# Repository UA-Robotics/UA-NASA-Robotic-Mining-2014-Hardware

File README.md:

# UA-NASA-Robotic-Mining-2014-Hardware

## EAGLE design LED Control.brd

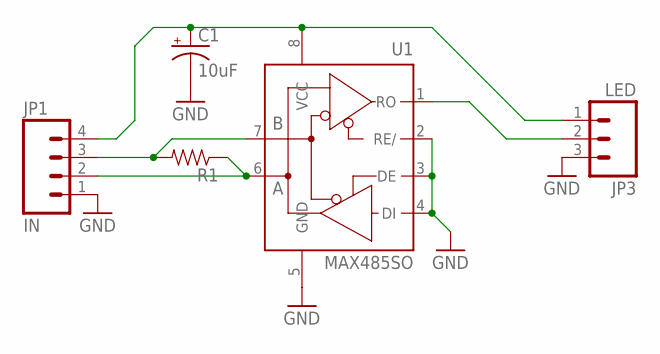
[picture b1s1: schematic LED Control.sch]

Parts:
C1: 10uF; EIA3216
JP1: IN; MOLEX-1X4_LOCK
JP3: LED; 1X03_LOCK
R1: RESISTOR0805-RES; 0805
U1: MAX485SO; SO08

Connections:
GND: C1.C (-), JP1.1, JP3.3, U1.2 (RE/), U1.3 (DE), U1.4 (DI), U1.5 (GND)
unnamed: JP1.3, R1.2, U1.7 (B)
unnamed: JP1.2, R1.1, U1.6 (A)
unnamed: C1.A (+), JP1.4, JP3.1, U1.8 (VCC)
unnamed: JP3.2, U1.1 (RO)

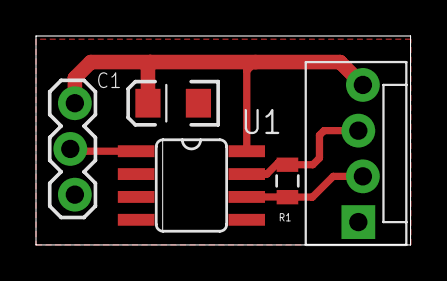
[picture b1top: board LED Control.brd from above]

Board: 2 copper layers, 20.8 x 11.6 mm, 5 parts (0 on the bottom side), 5 nets.

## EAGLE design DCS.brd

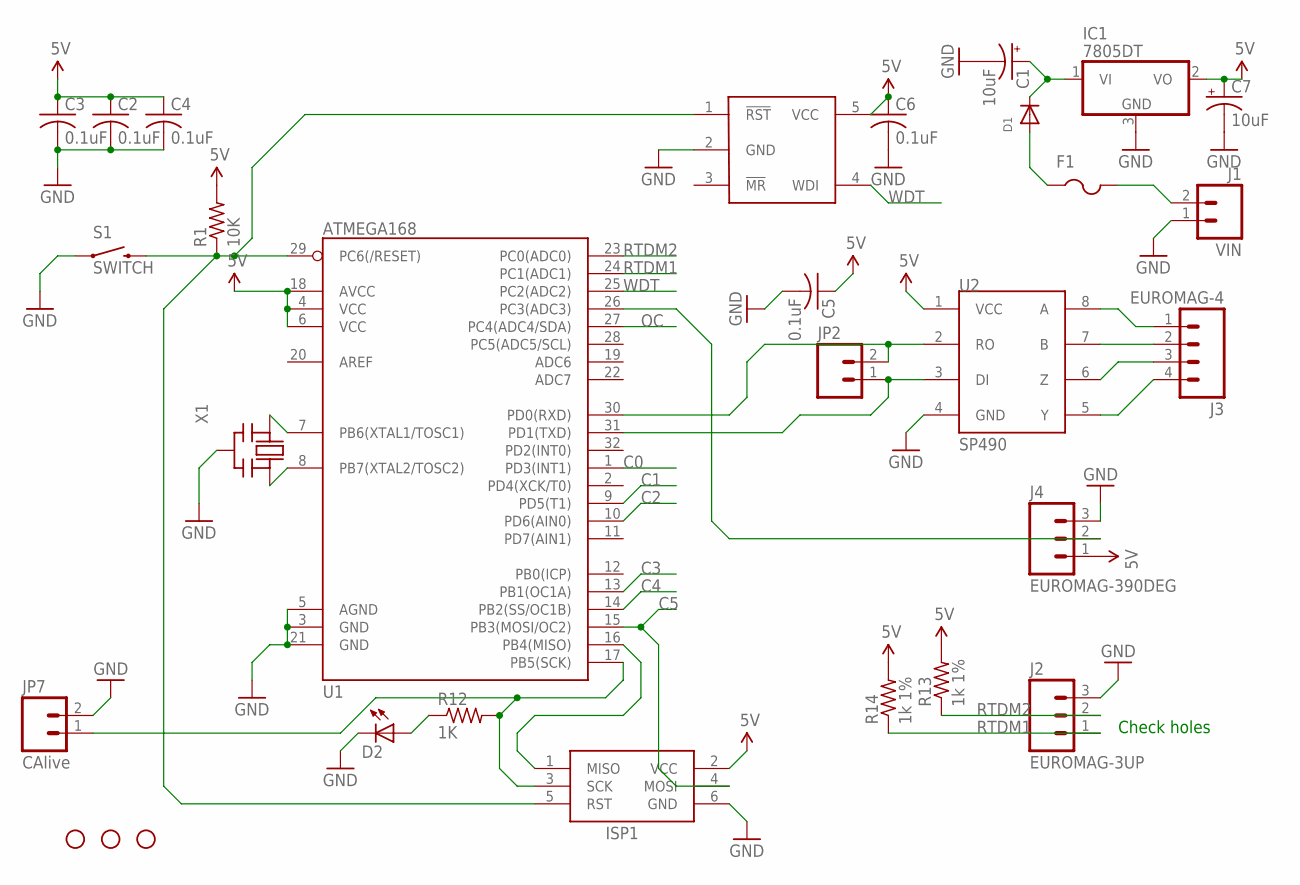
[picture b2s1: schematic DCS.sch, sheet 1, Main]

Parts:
C1: 10uF; CT6032
C2, C3, C4, C5, C6: 0.1uF; C0805
C7: 10uF; CT3216
D1: DIODESMA; SMADIODE
D2: LEDCHIPLED_0805; CHIPLED_0805
F1: PTCFUSE-1206; R1206
IC1: 7805DT; TO252
ISP1: AVRISP-6; AVRISP
J1: VIN; M2
J2: EUROMAG-3UP; M3-UP
J3: EUROMAG-4; M4
J4: EUROMAG-390DEG; M3
JP1, JP3, JP5: STAND-OFF
JP2: M02LOCK; 1X02_LOCK
JP7: CAlive; MOLEX-1X2_LOCK
R1: 10K; M0805
R12: 1K; M0805
R13, R14: 1k 1%; M0805
S1: SWITCH; TACTILE-PTH
U1: ATMEGA168; TQFP32-08
U2: SP490; SO08
U3: MAX823; SOT23-5L
X1: CERMOSCILL-AWCSR; AWCSR

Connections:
5V: C2.1, C3.1, C4.1, C5.1, C6.1, C7.+, IC1.2 (VO), ISP1.2 (VCC), J4.1, R1.2, R13.2, R14.2, U1.4 (VCC), U1.6 (VCC), U1.18 (AVCC), U2.1 (VCC), U3.5 (VCC); also elsewhere on the board
C0: U1.1 (PD3(INT1)); also elsewhere on the board
C1: U1.9 (PD5(T1)); also elsewhere on the board
C2: U1.10 (PD6(AIN0)); also elsewhere on the board
C3: U1.13 (PB1(OC1A)); also elsewhere on the board
C4: U1.14 (PB2(SS/OC1B)); also elsewhere on the board
C5: ISP1.4 (MOSI), U1.15 (PB3(MOSI/OC2)); also elsewhere on the board
GND: C1.-, C2.2, C3.2, C4.2, C5.2, C6.2, C7.-, D2.C, IC1.3 (GND), ISP1.6 (GND), J1.1, J2.3, J4.3, JP7.2, S1.1, U1.3 (GND), U1.5 (AGND), U1.21 (GND), U2.4 (GND), U3.2 (GND), X1.2 (GND); also elsewhere on the board
unnamed: JP2.2, U1.30 (PD0(RXD)), U2.2 (RO)
unnamed: F1.2, J1.2
unnamed: JP2.1, U1.31 (PD1(TXD)), U2.3 (DI)
unnamed: ISP1.5 (RST), R1.1, S1.3 (2), U1.29 (PC6(/RESET)), U3.1 (!RST)
unnamed: U1.8 (PB7(XTAL2/TOSC2)), X1.3 (OUT)
unnamed: J3.1, U2.8 (A)
unnamed: ISP1.1 (MISO), U1.16 (PB4(MISO))
unnamed: D1.A, F1.1
unnamed: U1.7 (PB6(XTAL1/TOSC1)), X1.1 (IN)
unnamed: D2.A, R12.1
unnamed: J3.2, U2.7 (B)
unnamed: J3.3, U2.6 (Z)
unnamed: C1.+, D1.C, IC1.1 (VI)
unnamed: J3.4, U2.5 (Y)
unnamed: J4.2, U1.26 (PC3(ADC3))
OC: U1.27 (PC4(ADC4/SDA)); also elsewhere on the board
RTDM1: J2.1, R14.1, U1.24 (PC1(ADC1))
RTDM2: J2.2, R13.1, U1.23 (PC0(ADC0))
SCLK: ISP1.3 (SCK), JP7.1, R12.2, U1.17 (PB5(SCK))
WDT: U1.25 (PC2(ADC2)), U3.4 (WDI)

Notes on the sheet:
Check holes

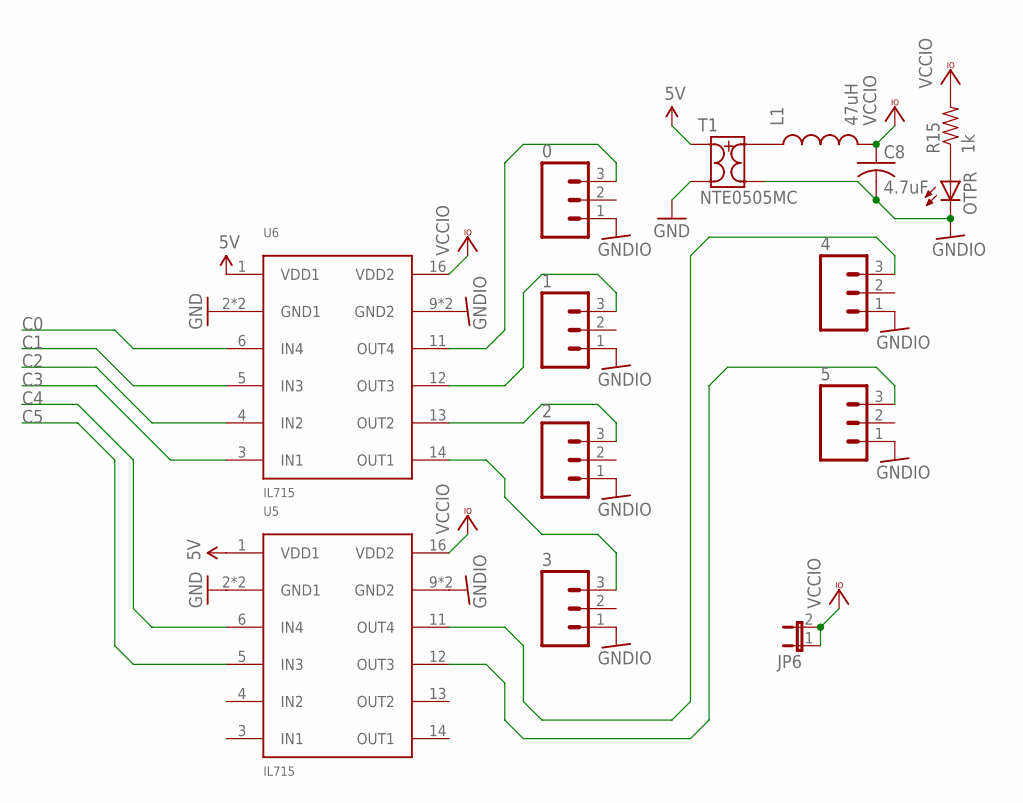
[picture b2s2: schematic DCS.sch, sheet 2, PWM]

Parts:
0, 1, 2, 3, 4, 5: M03PTH; 1X03
C8: 4.7uF; C0805
JP6: JUMPER-2SMD-NO; SJ_2S-NO
L1: 47uH; 0805
OTPR: LEDCHIP-LED0805; CHIP-LED0805
R15: 1k; 0805
T1: NTE0505MC; SO-8FT
U5, U6: IL715; S016

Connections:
5V: T1.3 (1), U5.1 (VDD1), U6.1 (VDD1); also elsewhere on the board
C0: U6.6 (IN4); also elsewhere on the board
C1: U6.5 (IN3); also elsewhere on the board
C2: U6.4 (IN2); also elsewhere on the board
C3: U6.3 (IN1); also elsewhere on the board
C4: U5.6 (IN4); also elsewhere on the board
C5: U5.5 (IN3); also elsewhere on the board
GND: T1.1 (2), U5.2 (GND1), U5.8 (GND1), U6.2 (GND1), U6.8 (GND1); also elsewhere on the board
GNDIO: 0.1, 1.1, 2.1, 3.1, 4.1, 5.1, C8.2, OTPR.C, T1.7 (3), U5.9 (GND2), U5.15 (GND2), U6.9 (GND2), U6.15 (GND2)
unnamed: OTPR.A, R15.1
unnamed: L1.1, T1.8 (4)
unnamed: 0.3, U6.11 (OUT4)
unnamed: 2.3, U6.13 (OUT2)
unnamed: 3.3, U6.14 (OUT1)
unnamed: 4.3, U5.11 (OUT4)
unnamed: 5.3, U5.12 (OUT3)
unnamed: 1.3, U6.12 (OUT3)
VCCIO: C8.1, JP6.1, JP6.2, L1.2, R15.2, U5.16 (VDD2), U6.16 (VDD2)

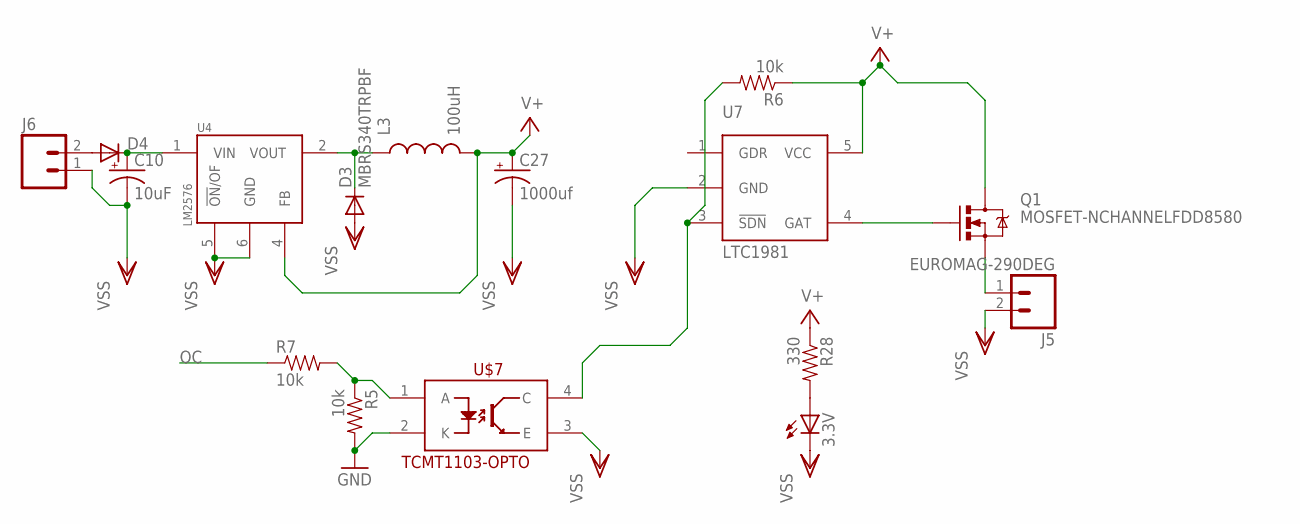
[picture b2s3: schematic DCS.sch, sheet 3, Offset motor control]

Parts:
3.3V: LEDCHIPLED_0805; CHIPLED_0805
C10: 10uF; EIA7343
C27: 1000uf; PANASONIC_G
D3: MBRS340TRPBF; SMC
D4: DIODESMB; SMB-DIODE
J5, J6: EUROMAG-290DEG; M2
L3: 100uH; INDUCTOR_5X3
Q1: MOSFET-NCHANNELFDD8580; DPAK
R5, R6, R7: 10k; 0805
R28: 330; 0805
U4: LM2576; TO-263-5
U7: LTC1981; SOT23-5L
U$7: TCMT1103-OPTO; SSOP-4

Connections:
GND: R5.2, U$7.2 (K); also elsewhere on the board
unnamed: D4.A, J6.2
unnamed: D3.C, L3.1, U4.2 (VOUT)
unnamed: Q1.1 (G), U7.4 (GAT)
unnamed: R6.2, U7.3 (!SDN), U$7.4 (C)
unnamed: J5.1, Q1.3 (S)
unnamed: R5.1, R7.2, U$7.1 (A)
unnamed: 3.3V.A, R28.2
OC: R7.1; also elsewhere on the board
V+: C27.+, L3.2, Q1.4 (D), R6.1, R28.1, U4.4 (FB), U7.5 (VCC)
VOLTIN: C10.A (+), D4.C, U4.1 (VIN)
VSS: 3.3V.C, C10.C (-), C27.-, D3.A, J5.2, J6.1, U4.5 (!ON!/OF), U4.6 (GND), U7.2 (GND), U$7.3 (E)

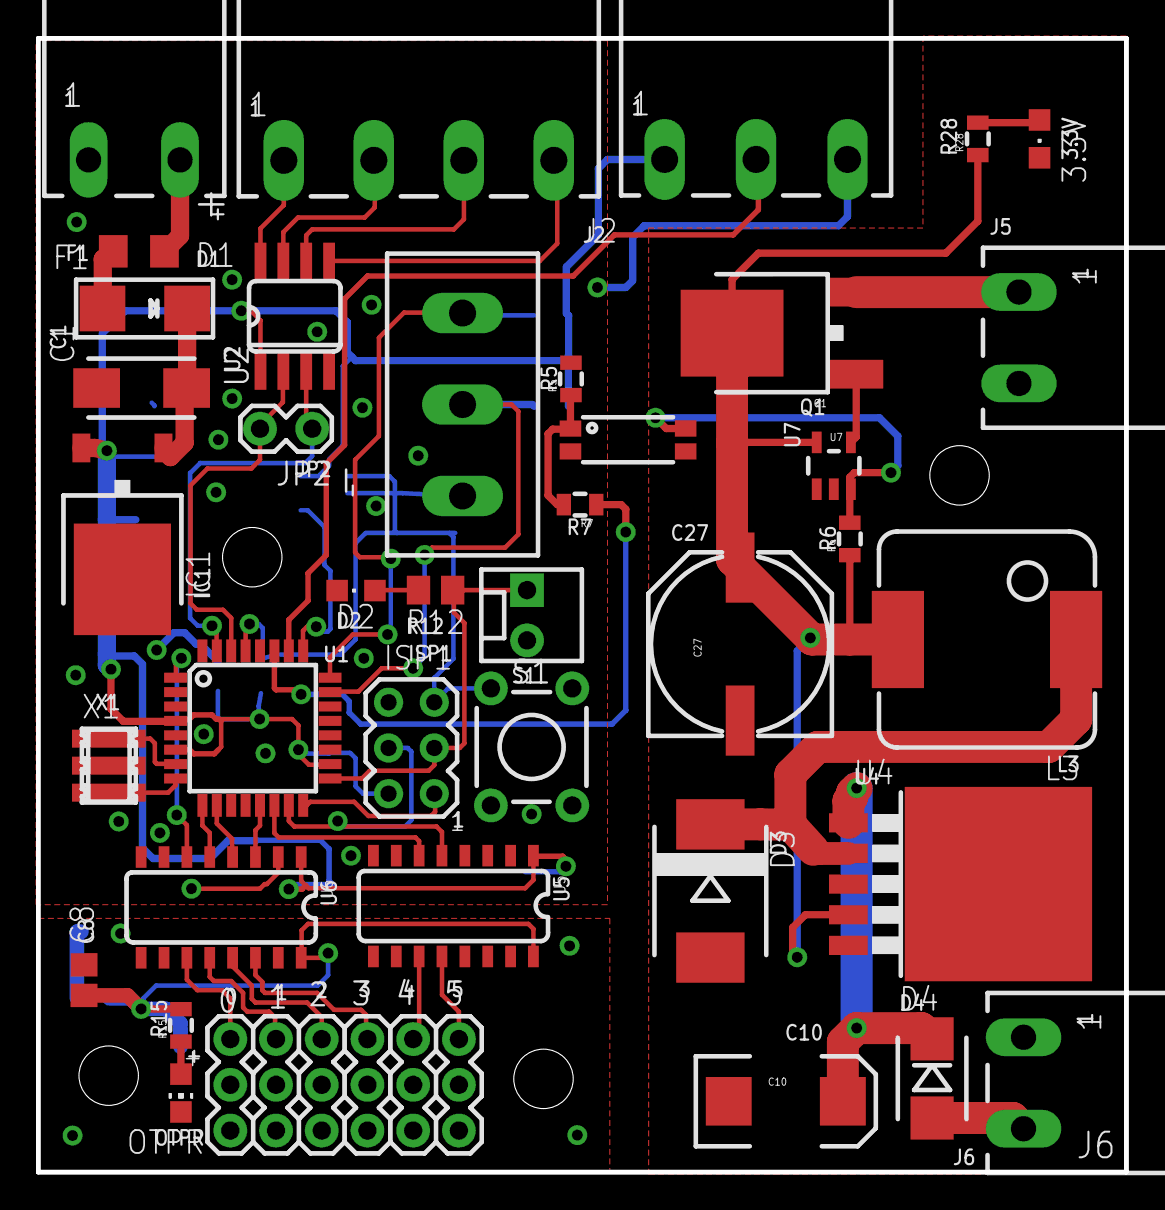
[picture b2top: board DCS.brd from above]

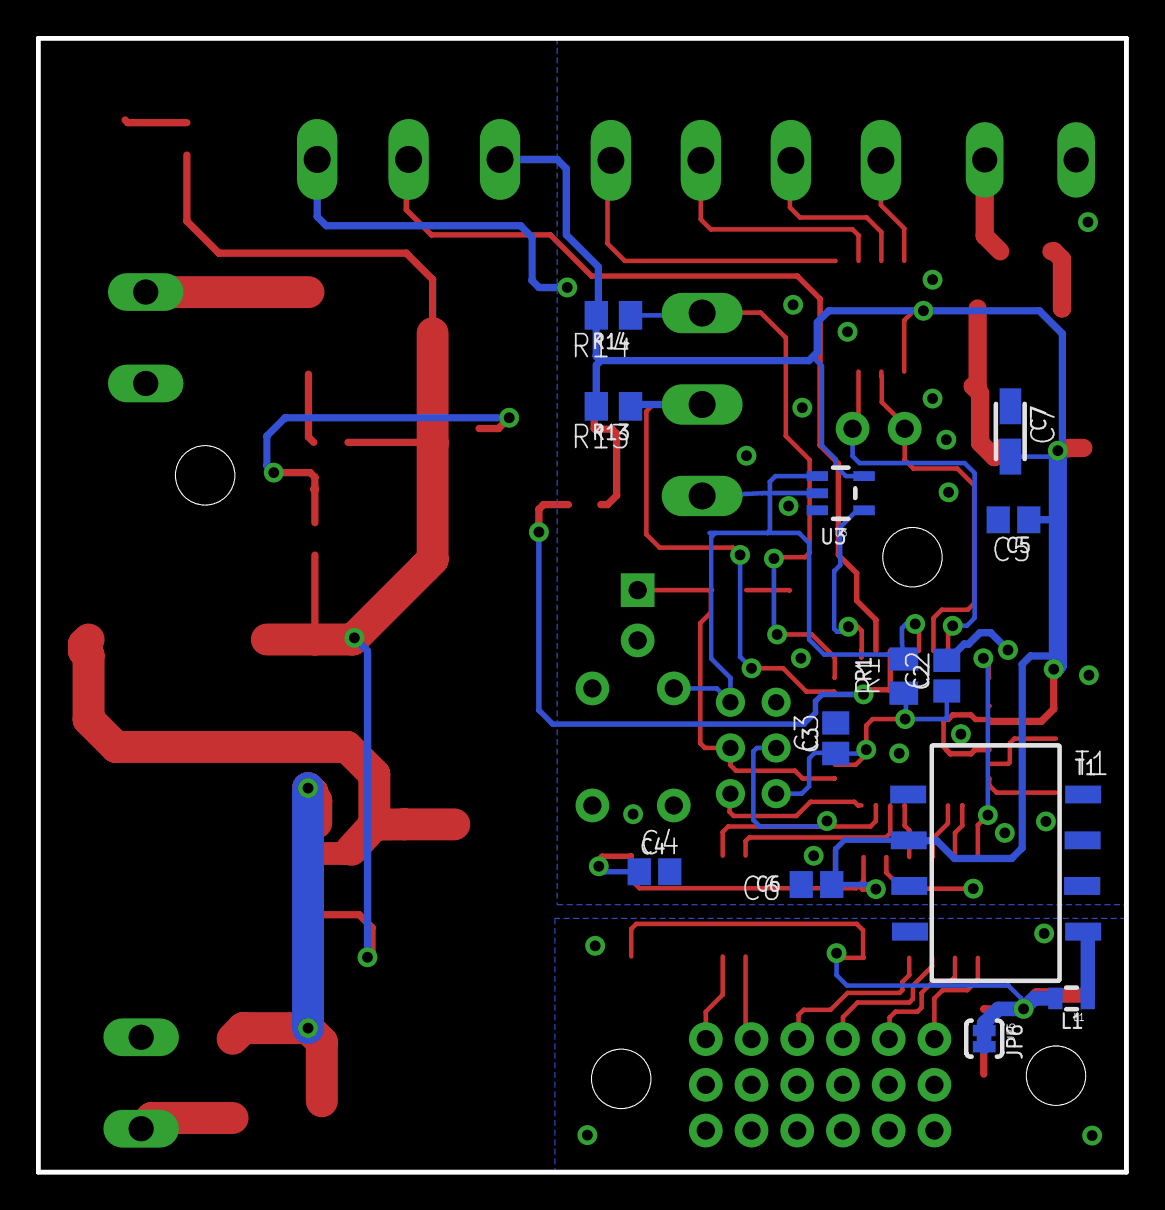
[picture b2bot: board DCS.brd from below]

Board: 2 copper layers, 60.5 x 63.0 mm, 61 parts (13 on the bottom side), 48 nets.

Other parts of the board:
JP4: STAND-OFF

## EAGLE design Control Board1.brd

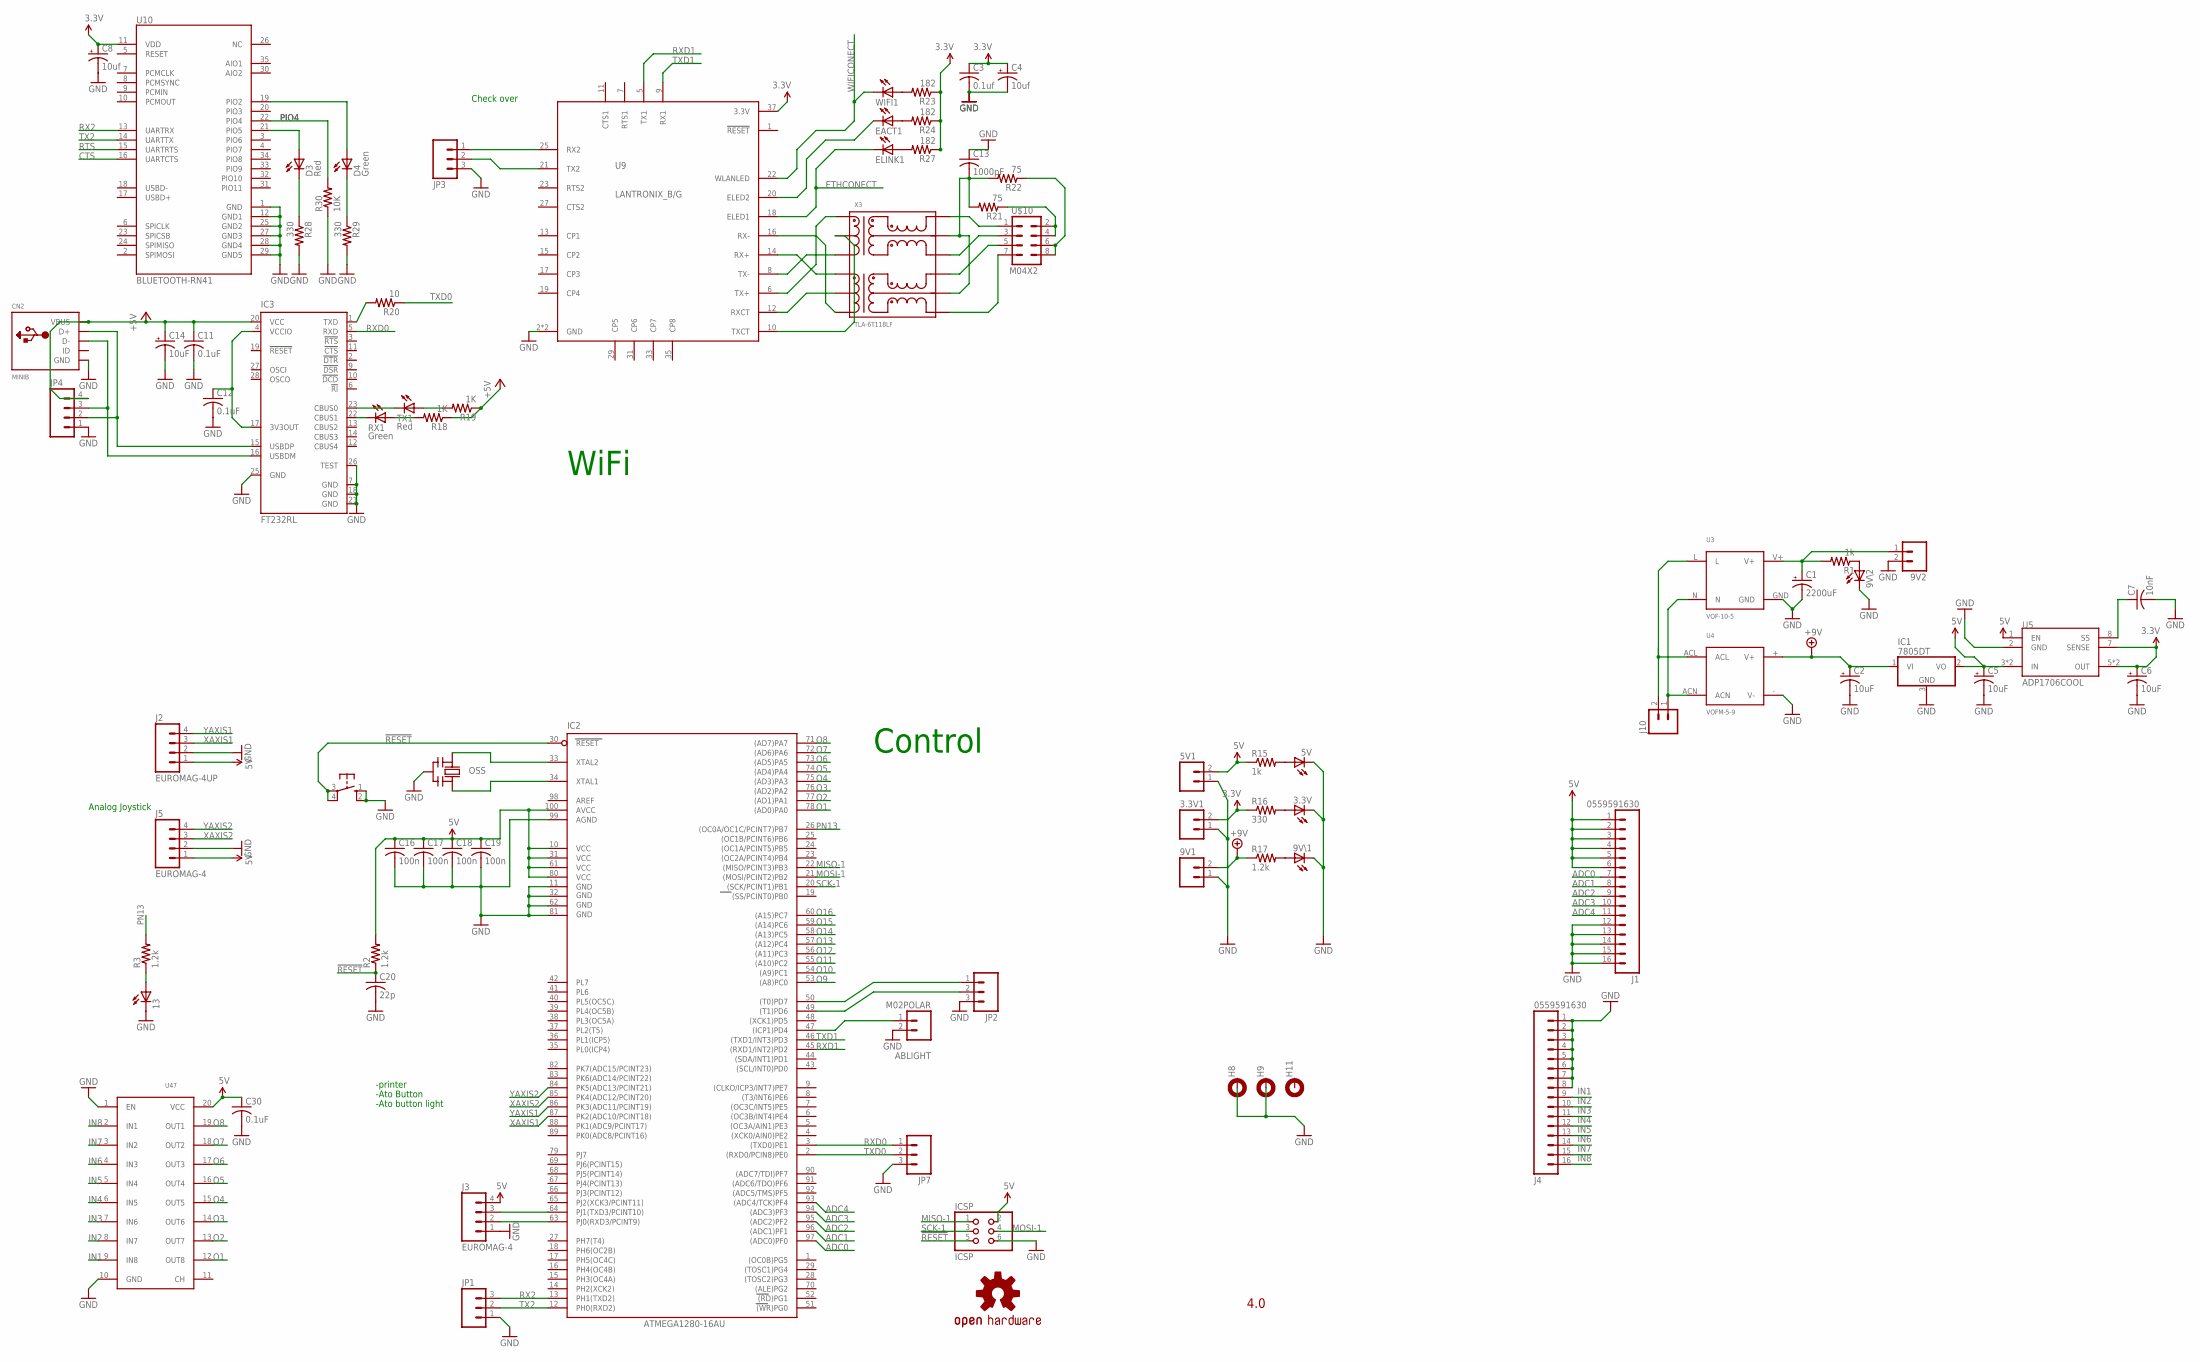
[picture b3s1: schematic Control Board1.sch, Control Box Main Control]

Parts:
3.3V, 5V, 9V\1, 9V\2: LED-FKIT-1206; FKIT-LED-1206
3.3V1, 5V1, 9V1, 9V2: EUROMAG-290DEG; M2
13: LEDCHIP-LED0805; CHIP-LED0805
ABLIGHT: M02POLAR; MOLEX-1X2
C1: 2200uF; EB20D
C2, C5, C6: 10uF; CT3528
C3: 0.1uf; C0805K
C4, C8: 10uf; EIA3528
C7: 10nF; C0805
C11, C12: 0.1uF; C0805K
C13: 1000pF; C1812
C14: 10uF; EIA3528-KIT
C16, C17, C18, C19: 100n; C0805
C20: 22p; C0805
C30: 0.1uF; C0805
CN2: MINIB; USB-MINIB
D3: Red; CHIP-LED0805
D4: Green; CHIP-LED0805
EACT1: LEDCHIP-LED0805; CHIP-LED0805
ELINK1: LEDCHIP-LED0805; CHIP-LED0805
H8, H9, H11: MOUNT-PAD-ROUND2.8; 2,8-PAD
IC1: 7805DT; TO252
IC2: ATMEGA1280-16AU; TQFP100
IC3: FT232RL; SSOP28
ICSP: ICSP; 2X03
J1, J4: 0559591630
J2: EUROMAG-4UP; M4-90
J3, J5: EUROMAG-4; M4
J10: EUROMAG-290DEG; M2
JP1, JP2, JP3: M03POLAR; MOLEX-1X3
JP4: M04LOCK; 1X04_LOCK
JP7: M03LOCK; 1X03_LOCK
OSS: CERMOSCILL-AWCSR; AWCSR
R1, R15: 1k; 0805
R2, R3, R17: 1.2k; 0805
R16, R28, R29: 330; 0805
R18, R19: 1K; R0805@1
R20: 10; R0805@1
R21, R22: 75; R0805@1
R23, R24, R27: 182; R0805@1
R30: 10K; 0805
RX1: Green; CHIP-LED0805
S1: 10-XX; B3F-10XX
TX1: Red; CHIP-LED0805
U3: VOF-10-5; VOF-10
U4: VOFM-5-9; VOFM-5
U5: ADP1706COOL; SO-8COOL
U9: LANTRONIX_B/G; LANA/BTH
U10: BLUETOOTH-RN41; RN41
U47: MAX6818; SSOP-20
U$3: OSHW-LOGOL; OSHW-LOGO-L
U$10: M04X2; 2X4
WIFI1: LEDCHIP-LED0805; CHIP-LED0805
X3: TLA-6T118LF; SO-16MOD

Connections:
3.3V: 3.3V1.2, C3.1, C4.A (+), C6.+, C8.A (+), R16.1, R23.1, R24.1, R27.1, U5.5 (OUT), U5.6 (OUT), U5.7 (SENSE), U9.37 (3.3V), U10.11 (VDD)
5V: 5V1.2, C5.+, C16.1, C17.1, C18.1, C19.1, C30.1, IC1.2 (VO), IC2.10 (VCC), IC2.31 (VCC1), IC2.61 (VCC2), IC2.80 (VCC3), IC2.100 (AVCC), ICSP.2, J1.1, J1.2, J1.3, J1.4, J1.5, J1.6, J2.1, J3.4, J5.1, R2.2, R15.1, U5.1 (EN), U5.3 (IN), U5.4 (IN), U47.20 (VCC)
!RESET: C20.1, IC2.30 (RESET), ICSP.5, R2.1, S1.3, S1.4 (P1)
+5V: C11.1, C14.A (+), CN2.VBUS, IC3.20 (VCC), JP4.4, R18.1, R19.1
+9V: 9V1.2, C2.+, IC1.1 (VI), R17.1, U4.+ (V+)
ADC0: IC2.97 ((ADC0)PF0), J1.7
ADC1: IC2.96 ((ADC1)PF1), J1.8
ADC2: IC2.95 ((ADC2)PF2), J1.9
ADC3: IC2.94 ((ADC3)PF3), J1.10
ADC4: IC2.93 ((ADC4/TCK)PF4), J1.11
CTS: U10.16 (UARTCTS)
D3: D3.C, R28.1
D4: D4.C, R29.1
ETHCONECT: ELINK1.C, U9.18 (ELED1)
GND: 3.3V.C, 3.3V1.1, 5V.C, 5V1.1, 9V1.1, 9V2.2, 9V\1.C, 9V\2.C, 13.C, ABLIGHT.2, C1.-, C2.-, C3.2, C4.C (-), C5.-, C6.-, C7.2, C8.C (-), C11.2, C12.2, C13.1, C14.C (-), C16.2, C17.2, C18.2, C19.2, C20.2, C30.2, CN2.GND, H8.B2,8, H9.B2,8, IC1.3 (GND), IC2.11 (GND), IC2.32 (GND1), IC2.62 (GND2), IC2.81 (GND3), IC2.99 (AGND), IC3.7 (GND), IC3.18 (GND), IC3.21 (GND), IC3.25 (GND), IC3.26 (TEST), ICSP.6, J1.12, J1.13, J1.14, J1.15, J1.16, J2.2, J3.1, J4.1, J4.2, J4.3, J4.4, J4.5, J4.6, J4.7, J4.8, J5.2, JP1.1, JP2.3, JP3.3, JP4.1, JP7.3, OSS.2 (GND), R28.2, R29.2, R30.1, S1.1 (S), S1.2 (S1), U3.GND, U4.- (V-), U5.2 (GND), U9.2 (GND), U9.39 (GND), U10.1 (GND), U10.12 (GND1), U10.25 (GND2), U10.27 (GND3), U10.28 (GND4), U10.29 (GND5), U47.1 (EN), U47.10 (GND)
IN1: J4.9, U47.9 (IN8)
IN2: J4.10, U47.8 (IN7)
IN3: J4.11, U47.7 (IN6)
IN4: J4.12, U47.6 (IN5)
IN5: J4.13, U47.5 (IN4)
IN6: J4.14, U47.4 (IN3)
IN7: J4.15, U47.3 (IN2)
IN8: J4.16, U47.2 (IN1)
MISO-1: IC2.22 ((MISO/PCINT3)PB3), ICSP.1
MOSI-1: IC2.21 ((MOSI/PCINT2)PB2), ICSP.4
unnamed: C7.1, U5.8 (SS)
unnamed: 13.A, R3.1
unnamed: R21.1, U$10.2, U$10.4
unnamed: R22.1, U$10.6, U$10.8
unnamed: U$10.5, X3.11
unnamed: IC2.34 (XTAL1), OSS.3 (OUT)
unnamed: IC2.33 (XTAL2), OSS.1 (IN)
unnamed: U$10.7, X3.9
unnamed: 9V\2.A, R1.1
unnamed: IC2.63 (PJ0(RXD3/PCINT9)), J3.2
unnamed: IC2.64 (PJ1(TXD3/PCINT10)), J3.3
unnamed: ABLIGHT.1, IC2.47 ((ICP1)PD4)
unnamed: IC2.50 ((T0)PD7), JP2.1
unnamed: IC2.49 ((T1)PD6), JP2.2
unnamed: JP3.1, U9.25 (RX2)
unnamed: JP3.2, U9.21 (TX2)
unnamed: 9V\1.A, R17.2
unnamed: 3.3V.A, R16.2
unnamed: 5V.A, R15.2
unnamed: J10.2, U3.L, U4.ACL
unnamed: J10.1, U3.N, U4.ACN
unnamed: 9V2.1, C1.+, R1.2, U3.V+
unnamed: CN2.D+, IC3.15 (USBDP), JP4.2
unnamed: CN2.D-, IC3.16 (USBDM), JP4.3
unnamed: IC3.23 (CBUS0), TX1.C
unnamed: IC3.22 (CBUS1), RX1.C
unnamed: R18.2, RX1.A
unnamed: R19.2, TX1.A
unnamed: IC3.1 (TXD), R20.2
unnamed: C12.1, IC3.4 (VCCIO), IC3.17 (3V3OUT)
unnamed: U9.8 (TX-), X3.3
unnamed: U9.6 (TX+), X3.1
unnamed: U9.14 (RX+), X3.6
unnamed: U9.16 (RX-), X3.8
unnamed: U9.12 (RXCT), X3.7
unnamed: U9.10 (TXCT), X3.2
unnamed: U$10.3, X3.14
unnamed: U$10.1, X3.16
unnamed: C13.2, R21.2, R22.2, X3.10, X3.15
unnamed: ELINK1.A, R27.2
unnamed: EACT1.A, R24.2
unnamed: R23.2, WIFI1.A
unnamed: EACT1.C, U9.20 (ELED2)
unnamed: D3.A, U10.21 (PIO5)
unnamed: D4.A, U10.19 (PIO2)
O1: IC2.78 ((AD0)PA0), U47.12 (OUT8)
O2: IC2.77 ((AD1)PA1), U47.13 (OUT7)
O3: IC2.76 ((AD2)PA2), U47.14 (OUT6)
O4: IC2.75 ((AD3)PA3), U47.15 (OUT5)
O5: IC2.74 ((AD4)PA4), U47.16 (OUT4)
O6: IC2.73 ((AD5)PA5), U47.17 (OUT3)
O7: IC2.72 ((AD6)PA6), U47.18 (OUT2)
O8: IC2.71 ((AD7)PA7), U47.19 (OUT1)
O9: IC2.53 ((A8)PC0)
O10: IC2.54 ((A9)PC1)
O11: IC2.55 ((A10)PC2)
O12: IC2.56 ((A11)PC3)
O13: IC2.57 ((A12)PC4)
O14: IC2.58 ((A13)PC5)
O15: IC2.59 ((A14)PC6)
O16: IC2.60 ((A15)PC7)
PIO4: R30.2, U10.22 (PIO4)
PN13: IC2.26 ((OC0A/OC1C/PCINT7)PB7), R3.2
RTS: U10.15 (UARTRTS)
RX2: IC2.13 (PH1(TXD2)), JP1.3, U10.13 (UARTRX)
RXD0: IC2.3 ((TXD0)PE1), IC3.5 (RXD), JP7.1
RXD1: IC2.45 ((RXD1/INT2)PD2), U9.5 (TX1)
SCK-1: IC2.20 ((SCK/PCINT1)PB1), ICSP.3
TX2: IC2.12 (PH0(RXD2)), JP1.2, U10.14 (UARTTX)
TXD0: IC2.2 ((RXD0/PCIN8)PE0), JP7.2, R20.1
TXD1: IC2.46 ((TXD1/INT3)PD3), U9.9 (RX1)
WIFICONECT: U9.22 (WLANLED), WIFI1.C
XAXIS1: IC2.87 (PK2(ADC10/PCINT18)), J2.3
XAXIS2: IC2.85 (PK4(ADC12/PCINT20)), J5.3
YAXIS1: IC2.86 (PK3(ADC11/PCINT19)), J2.4
YAXIS2: IC2.84 (PK5(ADC13/PCINT21)), J5.4

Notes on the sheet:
4.0
Control
Analog Joystick
WiFi
Check over
-printer
-Ato Button
-Ato button light

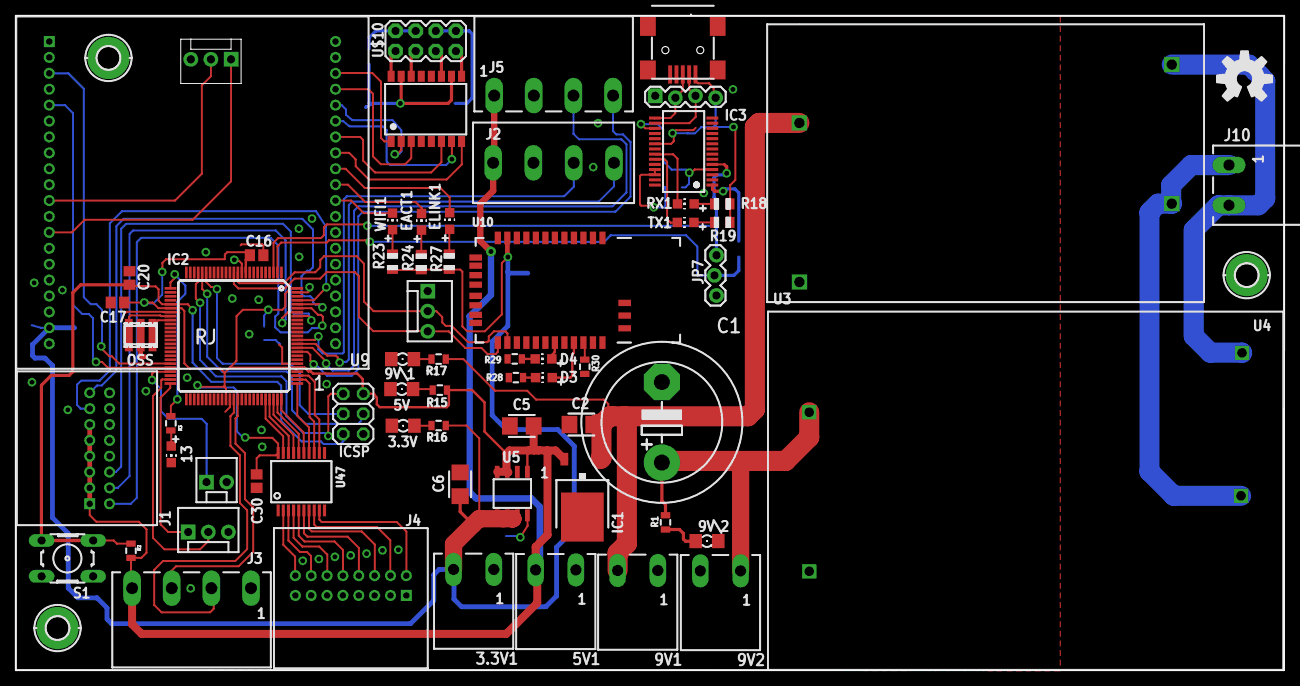
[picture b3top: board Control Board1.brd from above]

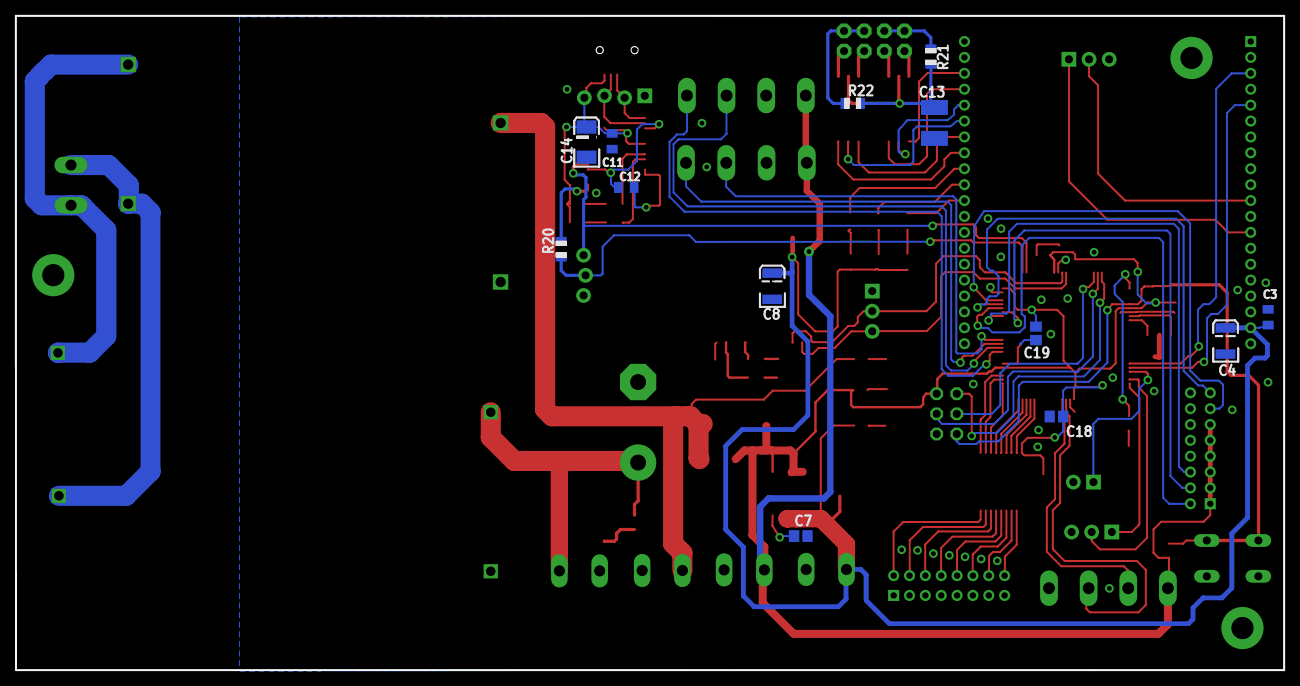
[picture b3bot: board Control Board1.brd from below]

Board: 2 copper layers, 160.0 x 82.5 mm, 82 parts (13 on the bottom side), 91 nets.

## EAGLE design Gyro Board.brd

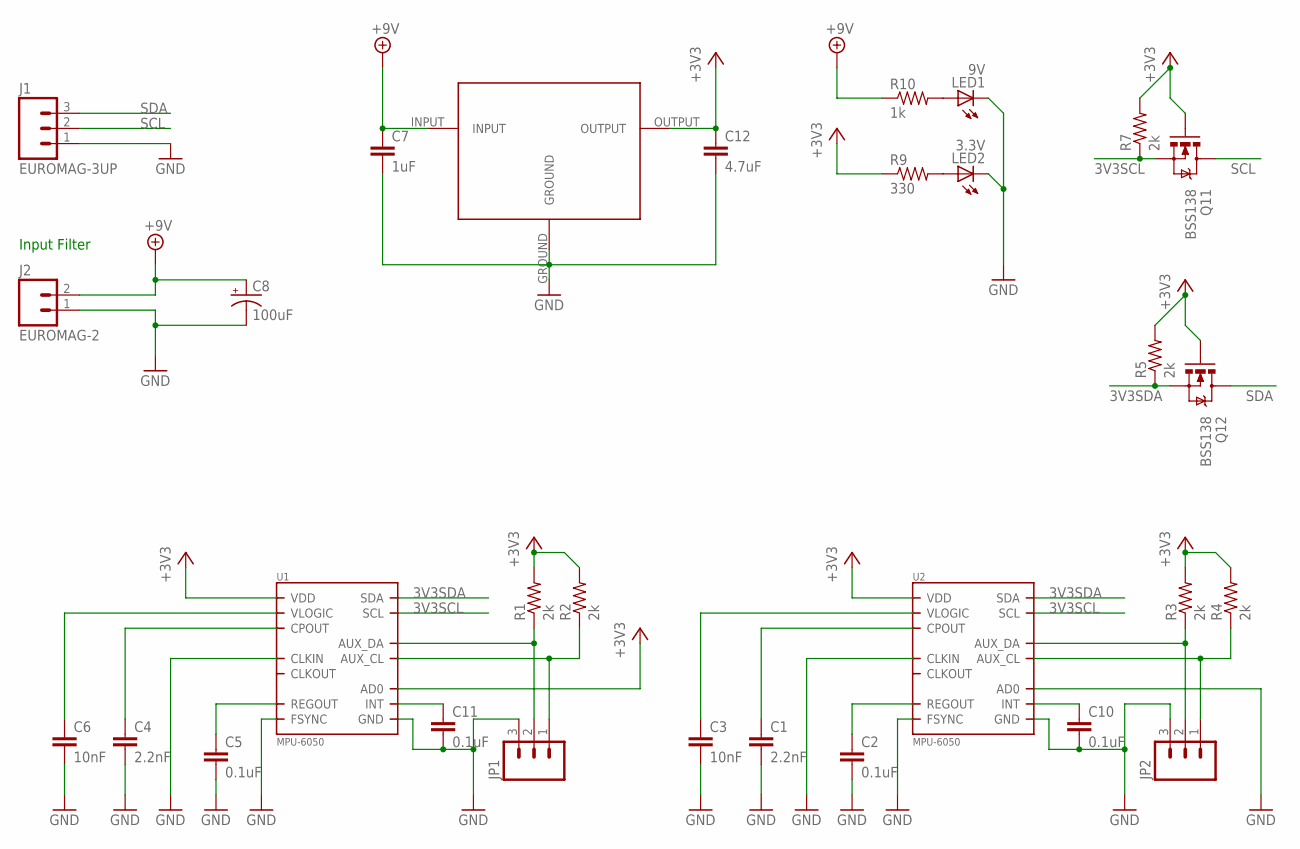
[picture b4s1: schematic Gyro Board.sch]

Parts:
3.3V: LP2950; TO-252
C1, C4: 2.2nF; 0805
C2, C5, C10, C11: 0.1uF; 0805
C3, C6: 10nF; 0805
C7: 1uF; 0805
C8: 100uF; 153CLV-0605
C12: 4.7uF; 0805
J1: EUROMAG-3UP; M3-UP
J2: EUROMAG-2; M2-UP
JP1, JP2: M03LOCK; 1X03_LOCK
LED1: 9V; CHIP-LED0805
LED2: 3.3V; CHIP-LED0805
Q11, Q12: BSS138; SOT23-3
R1, R2, R3, R4: 2k; M0805
R5, R7: 2k; R0805
R9: 330; 0805
R10: 1k; 0805
U1, U2: MPU-6050; QFN.24.4X4

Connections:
3V3SCL: Q11.2 (S), R7.1, U1.23 (SCL), U2.23 (SCL)
3V3SDA: Q12.2 (S), R5.1, U1.24 (SDA), U2.24 (SDA)
+3V3: 3.3V.OUTPUT, C12.1, Q11.1 (G), Q12.1 (G), R1.2, R2.2, R3.2, R4.2, R5.2, R7.2, R9.1, U1.9 (AD0), U1.13 (VDD), U2.13 (VDD)
+9V: 3.3V.INPUT, C7.1, C8.+, J2.2, R10.1
GND: 3.3V.GROUND, C1.2, C2.2, C3.2, C4.2, C5.2, C6.2, C7.2, C8.-, C10.2, C11.2, C12.2, J1.1, J2.1, JP1.3, JP2.3, LED1.C, LED2.C, U1.1 (CLKIN), U1.11 (FSYNC), U1.18 (GND), U2.1 (CLKIN), U2.9 (AD0), U2.11 (FSYNC), U2.18 (GND)
unnamed: JP1.2, R1.1, U1.6 (AUX_DA)
unnamed: JP1.1, R2.1, U1.7 (AUX_CL)
unnamed: JP2.2, R3.1, U2.6 (AUX_DA)
unnamed: JP2.1, R4.1, U2.7 (AUX_CL)
unnamed: C3.1, U2.8 (VLOGIC)
unnamed: C6.1, U1.8 (VLOGIC)
unnamed: C5.1, U1.10 (REGOUT)
unnamed: LED1.A, R10.2
unnamed: LED2.A, R9.2
unnamed: C4.1, U1.20 (CPOUT)
unnamed: C11.1, U1.12 (INT)
unnamed: C1.1, U2.20 (CPOUT)
unnamed: C10.1, U2.12 (INT)
unnamed: C2.1, U2.10 (REGOUT)
SCL: J1.2, Q11.3 (D)
SDA: J1.3, Q12.3 (D)

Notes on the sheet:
Input Filter

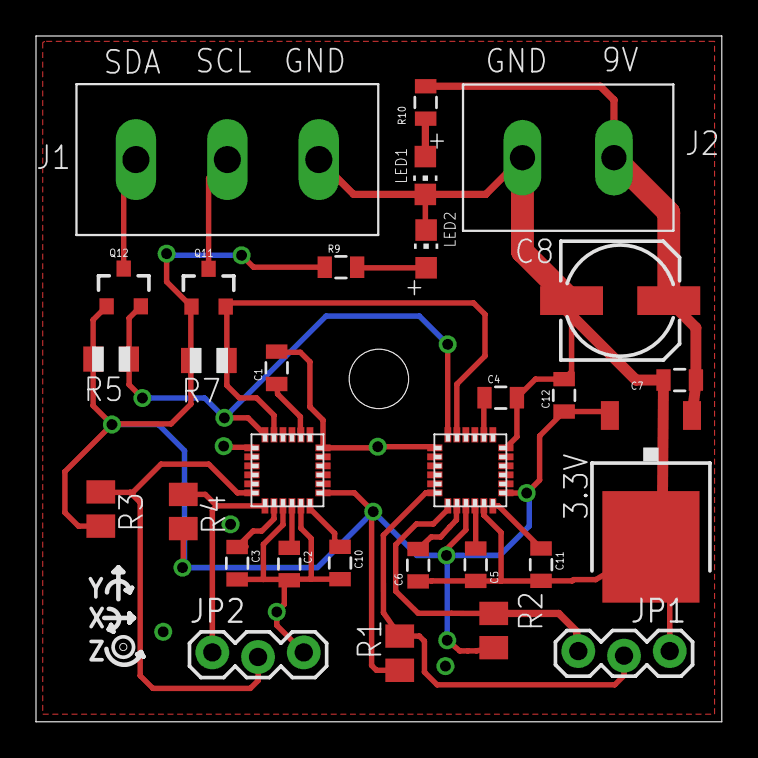
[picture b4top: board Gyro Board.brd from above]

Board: 2 copper layers, 38.1 x 38.1 mm, 31 parts (0 on the bottom side), 21 nets.

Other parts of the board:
U$3: STAND-OFF

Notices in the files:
parts and their libraries:
SparkFun-Connectors: Licensing: CC v3.0 Share-Alike You are welcome to use this library for commercial purposes.
